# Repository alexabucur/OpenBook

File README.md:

# OpenBook

## Prezentare generala

Proiectul a fost realizat in cadrul disciplinei _Testarea Sistemelor de Calcul_ si isi propune crearea unui model 3D detaliat pentru o tableta E-Book Reader. Am proiectat atat la nivel de circuit, cat si la nivel de design al produsului, folosind programul _Fusion360_ de la Autodesk.

## Block Diagram

## Bill of Materials
| Device | Description | Datasheet | Price per Unit | Link |
|----------------------|--------------------------------------|-----------|-----------|------|
| ADAFRUIT_LEDCHIP-LED0603 | LED | [datasheet](https://ro.mouser.com/datasheet/2/423/LSM0603412V-1379745.pdf) | 1,50 RON | [link](https://ro.mouser.com/ProductDetail/VCC/LSM0603412V?qs=sGAEpiMZZMt82OzCyDsLFG1ehM2%252BdxqbAopHlSxILTc%3D) |
| SJ | SMD solder JUMPER | [datasheet](https://www.farnell.com/datasheets/2813407.pdf) | 0,01 RON | [link](https://ro.farnell.com/panasonic/erj3gey0r00v/res-0r0-0-1w-0603-thick-film/dp/2059527) |
| ESP32_WROVER_EAGLE-LTSPICE_RR0402 | RESISTOR, European symbol | [datasheet](https://www.vishay.com/doc?28700) | 0,941 RON | [link](https://ro.mouser.com/ProductDetail/Vishay-Beyschlag/MCS04020D9101BE000?qs=sGAEpiMZZMvdGkrng054twKDKoBh%252BscnK%2FuqkNk9X%252BqO%2Fz5%2F0u93Ow%3D%3D) |
| 112A-TAAR-R03_ATTEND | Micro SD Card Socket, Push-Push Type, Top Mount, SMT, H=1.83mm, 10u | [datasheet](https://www.attend.com.tw/data/download/file/112A-TAAR-R03.pdf) | 1,54 RON | [link](https://www.soselectronic.com/ro-ro/products/attend/112a-taar-r03-116052) |
| EAGLE-LTSPICE_CC0402 | CAPACITOR, European symbol | [datasheet](https://ro.mouser.com/datasheet/2/40/Accu_P-3077555.pdf) | 5,74 RON | [link](https://ro.mouser.com/ProductDetail/KYOCERA-AVX/04025J0R5ZBSTR?qs=k4kUdCzLgS7v2DzbDWDPRw%3D%3D) |
| ESP32_WROVER_SPARKFUN-DISCRETESEMI_MOSFET_PCH-DMG2305UX-7 | P-channel MOSFETs | [datasheet](https://www.diodes.com/assets/Datasheets/DMG2305UX.pdf) | 0,941 RON | [link](https://ro.mouser.com/ProductDetail/Diodes-Incorporated/DMG2305UX-7?qs=L1DZKBg7t5F%2FNBHrjfxC%252Bg%3D%3D) |
| 744043680IND_4828-WE-TPC_WRE | | [datasheet](https://www.we-online.com/components/products/datasheet/744043680.pdf) | 6,44 RON | [link](https://ro.mouser.com/ProductDetail/Wurth-Elektronik/744043680?qs=PGXP4M47uW6VkZq%252BkzjrHA%3D%3D)|
| BD5229G-TR | Voltage Detector with Adjustable Delay Time | [datasheet](https://datasheet.datasheetarchive.com/originals/distributors/Datasheets_SAMA/f2b9741ef86007909f138d561a359946.pdf) | 3,72 RON | [link](https://ro.mouser.com/ProductDetail/ROHM-Semiconductor/BD5229G-TR?qs=4kLU8WoGk0vvnhrrYwdszw%3D%3D) |
| CPH3225A | Cap 0.011F 3.3V 1210 Flat | [datasheet](https://ro.mouser.com/datasheet/2/360/Seiko_Instruments_MicroBattery_E_20230330_2024Jan_-3561061.pdf) | 11,04 RON | [link](https://ro.mouser.com/ProductDetail/Seiko-Semiconductors/CPH3225A?qs=3etwrb1wR%252BhUOph6lAO7eg%3D%3D) | 
| DS3231SN# | Real Time Clock Serial 16-Pin SOIC W T/R | [datasheet](https://ro.mouser.com/datasheet/2/609/DS3231-3421123.pdf) | 73,80 RON | [link](https://ro.mouser.com/ProductDetail/Analog-Devices-Maxim-Integrated/DS3231SN?qs=1eQvB6Dk1vhUlr8%2FOrV0Fw%3D%3D) |
| ESP32-C6-WROOM-1-N8 | | [datasheet](https://ro.mouser.com/datasheet/2/891/Espressif_ESP32_C6_WROOM_1__Datasheet_V0_1_PRELIMI-3239987.pdf) | 14,70 RON | [link](https://ro.mouser.com/ProductDetail/Espressif-Systems/ESP32-C6-WROOM-1-N8?qs=8Wlm6%252BaMh8ST02Gmwp74cw%3D%3D) |
| ESP32_WROVER_AVX---SD0805S020S1R0_AVX_ SD0805S020S1R0_0_0AVX_SD0805S020S1R0_0_0 | Schottky Barrier Rectifier Diode | [datasheet](http://datasheets.avx.com/schottky.pdf) | 1,46 RON | [link](https://ro.mouser.com/ProductDetail/KYOCERA-AVX/SD0805S020S1R0?qs=jCA%252BPfw4LHbpkAoSnwrdjw%3D%3D) |
| ESP32_WROVER_BME680_BME680 | Integrated Environmental Unit | [datasheet](https://ro.mouser.com/datasheet/2/783/BST_BME680_DS001-1509608.pdf) | 40,69 RON | [link](https://ro.mouser.com/ProductDetail/Bosch-Sensortec/BME680?qs=v271MhAjFHjo0yA%2FC4OnDQ%3D%3D) |
| ESP32_WROVER_SPARKFUN-IC-POWER_MCP73831 | MCP73831T Li-Ion, Li-Pol Controller | [datasheet](https://ro.mouser.com/datasheet/2/268/MCP73831_Family_Data_Sheet_DS20001984H-3441711.pdf) | 3,57 RON | [link](https://ro.mouser.com/ProductDetail/Microchip-Technology/MCP73831T-4ADI-OT?qs=hH%252BOa0VZEiBTiqxSV9eepQ%3D%3D) |
| FH34SRJ-24S-0.5SH_99_ |  (0.50mm) Surface Mount, Right Angle | [datasheet](https://ro.mouser.com/datasheet/2/185/FH34SRJ_24S_0_5SH_99__CL0580_1255_6_99_2DDrawing_0-1615044.pdf) | 12,87 RON | [link](https://ro.mouser.com/ProductDetail/Hirose-Connector/FH34SRJ-24S-0.5SH99?qs=vcbW%252B4%252BSTIpKBl5ap9J8Fw%3D%3D) |
| MAX17048G+T10 |  | [datasheet](https://ro.mouser.com/datasheet/2/609/MAX17048_MAX17049-3469099.pdf) | 21,19 RON | [link](https://ro.mouser.com/ProductDetail/Analog-Devices-Maxim-Integrated/MAX17048G%2bT10?qs=D7PJwyCwLAoGnnn8jEPRBQ%3D%3D) |
| MBR0530 | ON SEMICONDUCTOR - MBR0530 - DIODE, SCHOTTKY, 0.5A, 30V, SOD-123 | [datasheet](https://www.onsemi.com/PowerSolutions/product.do?id=MBR0530T3G) | 0,89 RON | [link](https://ro.mouser.com/ProductDetail/onsemi/MBR0530T3G?qs=3JMERSakebpEmdUS6GetdQ%3D%3D) |
| PGB1010603MR |  | [datasheet](https://www.littelfuse.com/assetdocs/pulseguard-esd-suppressors-pgb1-datasheet?assetguid=8a337998-d54d-466b-be4e-dc5bcd1f9321) | 1,98 RON | [link](https://ro.mouser.com/ProductDetail/Littelfuse/PGB1010603MR?qs=gu7KAQ731URLg4GSnNNN7Q%3D%3D) |
| QWIIC_CONNECTORJS-1MM | SparkFun I2C Standard Qwiic Connector | [datasheet](https://ro.mouser.com/datasheet/2/813/Qwiic_Connector_Datasheet-1223982.pdf) | 2,75 RON | [link](https://ro.mouser.com/ProductDetail/SparkFun/PRT-14417?qs=wd5RIQLrsJhgdz%2FpmZ%2F3GQ%3D%3D) |
| SAMACSYS_PARTS_USB4110-GF-A | CONN USB 2.0 TYPE-C R/A SMT | [datasheet](https://ro.mouser.com/datasheet/2/837/GCT_USB4110_Product_Drawing___20k_cycles-3455479.pdf) | 5,84 RON | [link](https://ro.mouser.com/ProductDetail/GCT/USB4110-GF-A?qs=KUoIvG%2F9IlYiZvIXQjyJeA%3D%3D) |
| SI1308EDL-T1-GE3 | MOSFET N-Ch 30V 1.5A TrenchFET SC70 Vishay Si1308EDL-T1-GE3 N-channel MOSFET Transistor, 1.5 A, 30 V, 3-Pin SC-70 | [datasheet](https://www.vishay.com/doc?63399) | 2,07 RON | [link](https://ro.mouser.com/ProductDetail/Vishay-Semiconductors/SI1308EDL-T1-GE3?qs=bX1%252BNvsK%2FBramh9tgpOaEw%3D%3D) |
| USBLC6-2SC6Y | Low Cap. ESD Protection Auto SOT-23-6 STMicroelectronics  | [datasheet](https://ro.mouser.com/datasheet/2/389/usblc6_2sc6y-1852505.pdf) | 2,16 RON | [link](https://ro.mouser.com/ProductDetail/STMicroelectronics/USBLC6-2SC6Y?qs=gNDSiZmRJS%2FOgDexvXkdow%3D%3D) |
| W25Q512JVEIQ |  | [datasheet](https://ro.mouser.com/datasheet/2/949/Winbond_W25Q512JV_Datasheet-3240039.pdf) | 28,91 RON | [link](https://ro.mouser.com/ProductDetail/Winbond/W25Q512JVEIQ?qs=l7cgNqFNU1jw6svr3at6tA%3D%3D) |
| XC6220A331MR-G | LDO Voltage Regulators | [datasheet](https://ro.mouser.com/datasheet/2/760/xc6220-3371556.pdf) | 7,23 RON | [link](https://ro.mouser.com/ProductDetail/Torex-Semiconductor/XC6220A331MR-G?qs=AsjdqWjXhJ8ZSWznL1J0gg%3D%3D) |

## Functionalitate hardware
Componentele principale ale circuitului sunt:

+ USB C Connector + ESD Protection
  
 > destinat alimentarii E-Book, se conecteaza prin interfata USB
 
+ SD Card
 
 > Secure Digital Card este folosit ca si mediu de stocare pentru cartile in format electronic; lucreaza la 3.3V si se conecteaza cu microcontrollerul prin interfata SPI
 
+ E-Paper Display, impreuna cu modulele aferente - E-Paper Drive Circuit, E-Paper Display Header, EPD Power
  
> EPD Header se conecteaza prin interfata SPI la microcontroller, si realizeaza legatura intre celelalte componente
> EPD Power furnizeaza tensiuni multiple, iar E-Paper Drive Circuit genereaza semnalele necesare pentru controlul display-ului E-Paper
>
> display-ul consuma cel mai mult la refresh, 30mA daca este alb-negru si pana la 60mA pentru display color, iar in modul inactiv, dupa ce a afisat imaginea, consumul este chiar zero
 
+ Environmental Sensor BME688
  
 > este un senzor de mediu ce poate masura temperatura, umiditatea, presiunea atmosferica si calitatea aerului, care functioneaza la 3.3V si se conecteaza prin interfata I2C
>
> are un consum redus, in standby sub 1uA, iar pentru masurare foloseste intre 1-2mA

+ RTC Module DS3231SN
  
 > este un modul Real-Time Clock care are rolul de a pastra data si ora curenta atunci cand microcontroller-ul este oprit; poate functiona pe baterie, si are un cristal de 32KHz integrat; se conecteaza la ESP32-C6 prin I2C, folosind pinii SCL si SDA
>
> consumul sau tipic variaza de la 150uA, atunci cand este alimentat de la sursa principala, si scade la 1uA la trecerea pe baterie

+ External NOR Flash 64MB
  
> extinde memoria microcontroller-ului, aici se stocheaza date suplimentare, se poate face si o stocare temporara; foloseste interfata SPI
> 
> contributia sa la consumul energetic total este foarte mica; cel mai mult se consuma la stergerea din flash (in jur de 50mA), respectiv la scriere (30-50mA); in standby se consuma numai 10-20uA

+	LDO Voltage Regulator
  
> este un stabilizator de tensiune liniar, care asigura tensiunea de iesire constanta la valoarea de 3.3V pentru microcontroller;
>
> are un consum energetic foarte mic (in jur de 8uA atunci cand este activ), ceea ce il face ideal pentru dispozitive alimentate pe baza de baterie, precum cel de fata

+ Voltage Supervisor
  
> folosit pentru monitorizeaza nivelului tensiunii, si pentru a asigura ca sistemul nu poate porni atunci cand avem o tensiune instabila sau mult prea mica

+ Qwiic/Stemma QT
  
> simplifica atasarea senzorilor si perifericelor la microcontroller, facand posibila conectarea mai multor dispozitive in lant, fara a fi nevoie de fire distincte pentru fiecare semnal; functioneaza pe baza protocolului I2C

+ Li-Po Battery Controller

> gestioneaza incarcarea/descarcarea bateriei, regland constant tensiunea si curentul;  la alimentarea bateriei, previne supraincarcarea , iar la descarcare monitorizeaza tensiunea pentru a evita descarcarea profunda; este conectat la sursa de alimentare si la baterie

## Microcontroller - ESP32-C6
Intreg circuitul a fost conceput in jurul microcontrollerului ESP32-C6-WROOM, care este un modul preasamblat, si principalul consumator energetic al circuitului. Consumul mediu se situeaza undeva intre 100uA si 2mA, avand in vedere ca in modul _Activ_ se consuma in jur de 100-120mA, in _Idle_ 10-15mA iar atunci cand se afla in _Deep Sleep_ doar 10-20uA. In mod evident, consumul depinde cel mai mult de durata sesiunilor active.
> Placa ESP-WROOM-32 dispune de o varietate de interfete pentru conectarea altor componente si senzori, inclusiv pini de I/O, SPI, I2C si UART. Aceastea faciliteaza integrarea si extind gama de aplicatii posibile. Placa foloseste WiFi 6 2.4 GHz, are integrat Bluetooth 5 si antena.
>> 
> ESP32-C6 se leaga de cele mai importante module ale circuitului prin intermediul pinilor sai:
> - **Alimentare si reset**
>> **3V3** asigura alimentrea modulului, **GND** legatura la masa, **EN** trebuie sa fie pe pozitia _HIGH_ pentru ca modulul sa functioneze (EN va fi controlat de catre butonul RESET)
> - **USB C Connector**
>> deoarece ESP32-C6 are USB nativ, conexiunea se realizeaza direct prin liniile de date **USB_D+** si **USB_D-**, la pinii **GPIO13** si **GPIO14** ai modulului; nu mai este deci nevoie de un convertor serial extern
> - **SD Card**
>> pentru a comunica cu dispozitive rapide precum SD Card se foloseste interfata SPI(Serial Peripheral Interface), folosind pinii **GPIO27(MISO)** - pentru transfer de la card la ESP, **GPIO7(MOSI)** - pentru transfer invers, **GPIO6(SCK)** -semnalul de ceas care asigura sincronizarea, respectiv **GPIO4(SS_SD)** - chip select
> - **E-Paper Display**
>> pentru conexiunea si controlul ecranului dispozitivului se folosesc pinii **GPIO11(EPD_CS)** - Chip Select pentru display-ul EPD, **GPIO5(EPD_DC)** - pentru controlul display-ului, **GPIO21(EPD_RST)** - pentru resetarea display-ului, respectiv **GPIO26(EPD_BUSY)**
> - **Environmental Sensor BME688**
>> avand in vedere ca se face comunicatia cu senzorul prin intermediul protocolului I2C, pentru stabilirea legaturii se vor folosi pinii **GPIO19(SDA)**, **GPIO20(SCL)** si **GPIO17(I2C_PW)** de pe microcontroller
> - **UART(Serial Communication)**
>> ESP32-C6 are si interfete seriale, utile pentru debugging sau conexiuni cu alte dispozitive; pinii aferenti comunicarii UART sunt **TXD0** -pentru transmisia datelor respectiv **RXD0** - pentru receptie de date
> - **Restul pinilor**
>> - **FLASH_CS** este un pin Chip Select pentru selectarea chipului flash extern (pentru comunicarea SPI cu External NOR Flash)
>> - **IO/BOOT** folosit pentru a intra in boot mode – legatura cu butonul de _boot_
>> - **RTC_PWM** pentru semnale Pulse Width Modulation trimise catre Real Time Clock
>> - **RTC_RST** pentru resetarea ceasului
>> - **INT_RTC** destinat semnalelor de intrerupere de la modulul RTC, de exemplu in cazul iesirii din moduri de functionare (sleep), pentru executarea unor sarcini periodice, cum ar fi un refresh al display-ului etc.

## Amplasarea componentelor / Reguli de design

La design-ul PCB-ului am tinut cont de cateva aspecte importante in ceea ce priveste amplasarea componentelor pe placuta. Astfel:

+ **Microcontroller-ul ESP32** se afla in marginea de sus a PCB-ului, cu antena inspre exterior si cu PCB-ul decupat in aceasta zona, pentru ca antena sa nu fie blocata si pentru a se evita orice interferente
+ **Conectorul USB** se afla in partea de jos a placutei, centrat astfel incat sa se alinieze cu orificiul din carcasa si sa permita conectarea mufei USB-C
+ **E-Paper Display Header** este pozitionat pe lateral, iar in dreptul sau exista un decupaj in PCB - acesta este spatiul in care se va introduce ribbon-ul display-ului nostru
+  **Conectorul Qwiic** e amplasat pe marginea PCB-ului, si s-a lasat suficient spatiu in jurul sau, pentru a permite conectarea facila a unor cabluri suplimentare
+  PCB-ul este decupat intr-o zona suficient de mare in care sa incapa si bateria device-ului
## Errors

La editarea PCB-ului in Fusion 360 am intampinat urmatoarele erori:

Erorile au aparut din cauza dimensiunii gaurilor din mufa USB, asa ca le-am aprobat pe amandoua.

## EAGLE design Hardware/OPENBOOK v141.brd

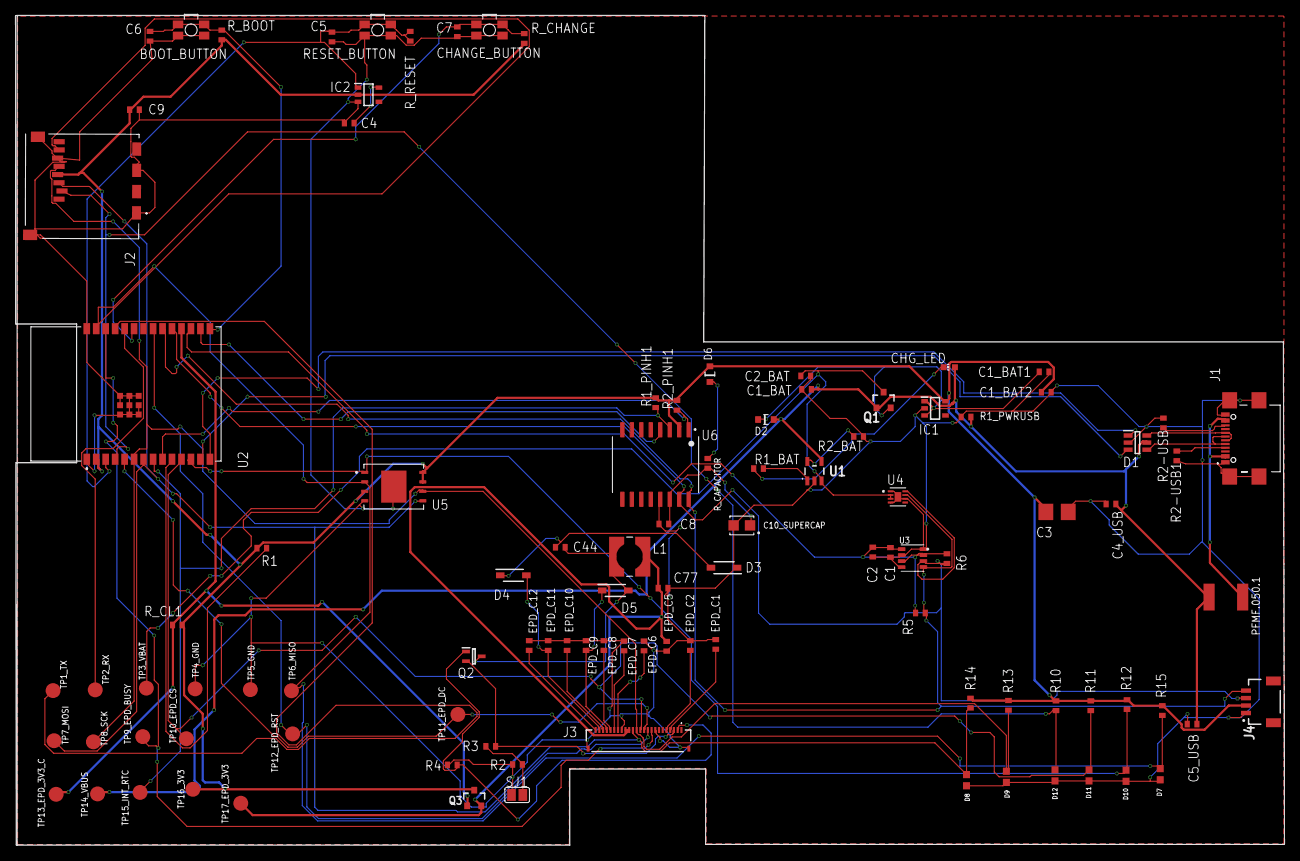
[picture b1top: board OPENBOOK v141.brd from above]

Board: 2 copper layers, 170.1 x 111.2 mm, 103 parts (0 on the bottom side), 55 nets.

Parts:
BOOT_BUTTON: BUTTON_CUSYOMV1; MYBUTTON
C1, C2, C4, C4_USB, C6, C7, C8, C9: 100nF; EAGLE-LTSPICE_C0402
C1_BAT, C1_BAT1, C1_BAT2, C2_BAT, C5_USB: 4.7uF; EAGLE-LTSPICE_C0402
C3: 100uF; RCL_CT3528
C5: 1uF; EAGLE-LTSPICE_C0402
C10_SUPERCAP: CPH3225A; CAPCP3225X100N
C44: 4.7uF/25V; EAGLE-LTSPICE_C0402
C77: 10uF; EAGLE-LTSPICE_C0402
CHANGE_BUTTON: BUTTON_CUSYOMV1; MYBUTTON
CHG_LED: ADAFRUIT_CHIP-LED0603
D1: USBLC6-2SC6Y; SOT95P280X145-6N
D2, D6: ESP32_WROVER_AVX---SD0805S020S1R0_AVX_SD0805S020S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; ESP32_WROVER_AVX---SD0805S020S1R0_AVX_SD0805S020S1R0_0
D3, D4, D5: MBR0530; SOD3716X135N
D7, D8, D9, D10, D11, D12: PGB1010603MR; DIOC1608X36N
EPD_C1, EPD_C2, EPD_C6, EPD_C7, EPD_C8, EPD_C9, EPD_C10, EPD_C11, EPD_C12: 1uF/50V; EAGLE-LTSPICE_C0402
EPD_C5: 0.1uF/50V; EAGLE-LTSPICE_C0402
IC1: XC6220A331MR-G; SOT95P280X120-5N
IC2: BD5229G-TR; SOT95P280X125-5N
J1: SAMACSYS_PARTS_USB4110-GF-A; SAMACSYS_PARTS_USB4110GFA
J2: 112A-TAAR-R03_ATTEND; 112ATAARR03ATTEND
J3: FH34SRJ-24S-0.5SH_99_; FH34SRJ24S05SH99
J4: QWIIC_RIGHT_ANGLE; JST04_1MM_RA
L1: 68uH; IND_4828-WE-TPC_WRE
PFMF.050.1: ESP32C6_VARISTORCN1812; ESP32C6_VARISTOR_CT/CN1812
Q1, Q3: 20V/4.2A/52mΩ/1.4W; ESP32_WROVER_SPARKFUN-DISCRETESEMI_SOT23-3
Q2: SI1308EDL-T1-GE3; SOT65P210X110-3N
R1, R1_PINH1, R2_PINH1, R4, R5, R6, R10, R11, R12, R13, R14, R15: 10K; ESP32_WROVER_EAGLE-LTSPICE_R0402
R1_BAT: 200; ESP32_WROVER_EAGLE-LTSPICE_R0402
R1_PWRUSB: 100K; ESP32_WROVER_EAGLE-LTSPICE_R0402
R2: 2.2; ESP32_WROVER_EAGLE-LTSPICE_R0402
R2-USB, R2-USB1: 5k1; ESP32_WROVER_EAGLE-LTSPICE_R0402
R2_BAT: 2K; ESP32_WROVER_EAGLE-LTSPICE_R0402
R3: 0.47; ESP32_WROVER_EAGLE-LTSPICE_R0402
RESET_BUTTON: BUTTON_CUSYOMV1; MYBUTTON
R_BOOT: 10K; ESP32_WROVER_EAGLE-LTSPICE_R0402
R_CAPACITOR: ESP32_WROVER_EAGLE-LTSPICE_R0402
R_CHANGE: 10K; ESP32_WROVER_EAGLE-LTSPICE_R0402
R_CL1: 10K; ESP32_WROVER_EAGLE-LTSPICE_R0402
R_RESET: 10K; ESP32_WROVER_EAGLE-LTSPICE_R0402
SJ1: SJ
TP1_TX, TP2_RX, TP3_VBAT, TP4_GND, TP5_GND, TP6_MISO, TP7_MOSI, TP8_SCK, TP9_EPD_BUSY, TP10_EPD_CS, TP11_EPD_DC, TP12_EPD_RST, TP13_EPD_3V3_C, TP14_VBUS, TP15_INT_RTC, TP16_3V3, TP17_EPD_3V3: TPTP20R; TP20R
U1: ESP32_WROVER_SPARKFUN-IC-POWER_MCP73831; ESP32_WROVER_SPARKFUN-IC-POWER_SOT23-5
U2: ESP32-C6-WROOM-1-N8; XCVR_ESP32-C6-WROOM-1-N8
U3: ESP32_WROVER_BME680_BME680; ESP32_WROVER_BME680_PSON80P300X300X100-8N
U4: MAX17048G+T10; SON50P200X200X80-9N
U5: W25Q512JVEIQ; SON127P600X800X80-9N
U6: DS3231SN#; SOIC127P1032X265-16N

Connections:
3V3: C1_BAT2.1, C3.+, C9.1, D6.2, IC1.5, IC2.2, J2.P4, J4.2, Q3.3, R1.2, R1_PINH1.2, R2_PINH1.2, R10.2, R11.2, R12.2, R13.2, R14.2, R15.2, R_BOOT.2, R_CHANGE.2, R_CL1.2, TP16_3V3.TP, U2.2, U5.3, U5.7, U5.8, U6.2
32KHZ: R2_PINH1.1, U2.9, U6.1
DN: D1.4, J1.A7, J1.B7
DP: D1.6, J1.A6, J1.B6
EPD_3V3: C77.1, EPD_C5.1, J3.15, J3.16, L1.2, Q3.2, TP17_EPD_3V3.TP
EPD_3V3_C: Q3.1, R_CL1.1, TP13_EPD_3V3_C.TP, U2.18
EPD_BUSY: J3.9, TP9_EPD_BUSY.TP, U2.26
EPD_CS: D11.2, J3.12, R11.1, TP10_EPD_CS.TP, U2.11
EPD_DC: J3.11, TP11_EPD_DC.TP, U2.5
EPD_RST: J3.10, TP12_EPD_RST.TP, U2.21
FLASH_CS: D10.2, R12.1, U2.12, U5.1
GDR: J3.2, Q2.1, R4.2
GND: BOOT_BUTTON.1, BOOT_BUTTON.2, C1.2, C1_BAT.2, C1_BAT1.2, C1_BAT2.2, C2.2, C2_BAT.2, C3.-, C4.2, C4_USB.2, C5.2, C5_USB.2, C6.2, C7.2, C8.2, C9.2, C10_SUPERCAP.2, C77.2, CHANGE_BUTTON.1, CHANGE_BUTTON.2, D1.2, D3.1, D7.1, D8.1, D9.1, D10.1, D11.1, D12.1, EPD_C1.2, EPD_C2.2, EPD_C5.2, EPD_C6.2, EPD_C7.2, EPD_C8.2, EPD_C9.2, EPD_C10.2, EPD_C11.2, EPD_C12.2, IC1.2, IC2.3, J1.A1, J1.A12, J1.B1, J1.B12, J1.MP1, J1.MP2, J1.MP3, J1.MP4, J2.G1, J2.G2, J2.G3, J2.G4, J2.P6, J3.8, J3.17, J3.MP1, J3.MP2, J4.1, R1_PWRUSB.1, R2.1, R2-USB.2, R2-USB1.1, R2_BAT.1, R4.1, RESET_BUTTON.1, RESET_BUTTON.2, SJ1.1, TP4_GND.TP, TP5_GND.TP, U1.2, U2.1, U2.28, U2.29_1, U2.29_2, U2.29_3, U2.29_4, U2.29_5, U2.29_6, U2.29_7, U2.29_8, U2.29_9, U3.1, U3.5, U3.7, U4.1, U4.4, U4.6, U4.9, U5.4, U5.9, U6.13
GPIO8: R1.1, U2.10
I2C_PW: C1.1, C2.1, R5.2, R6.2, U2.17, U3.2, U3.6, U3.8
INT_RTC: R1_PINH1.1, TP15_INT_RTC.TP, U2.8, U6.3
IO/BOOT: BOOT_BUTTON.3, BOOT_BUTTON.4, C6.1, R_BOOT.1, U2.15
IO/CHANGE: C7.1, CHANGE_BUTTON.3, CHANGE_BUTTON.4, R_CHANGE.1, U2.23
MISO: D7.2, J2.P7, R15.1, TP6_MISO.TP, U2.27, U5.2
MOSI: D8.2, J2.P3, J3.14, R14.1, TP7_MOSI.TP, U2.7, U5.5
unnamed: J1.B5, R2-USB.1
unnamed: C1_BAT1.1, D2.1, IC1.1, IC1.3, Q1.2
unnamed: R1_BAT.2, U1.1
unnamed: CHG_LED.C, R1_BAT.1
unnamed: EPD_C1.1, J3.4
unnamed: R2_BAT.2, U1.5
unnamed: EPD_C2.1, J3.5
unnamed: C44.1, D3.2, D4.1
unnamed: J1.A5, R2-USB1.2
unnamed: C4.1, IC2.5
unnamed: EPD_C6.1, J3.18
unnamed: EPD_C7.1, J3.19
unnamed: EPD_C8.1, J3.20
unnamed: EPD_C10.1, J3.22
unnamed: EPD_C12.1, J3.24
unnamed: D6.1, R_CAPACITOR.1
PREVGH: D5.1, EPD_C9.1, J3.21
PREVGL: D4.2, EPD_C11.1, J3.23
RESE: J3.3, Q2.2, R3.2
RESE': R2.2, R3.1, SJ1.2
RESET: C5.1, IC2.1, RESET_BUTTON.3, RESET_BUTTON.4, R_RESET.1, R_RESET.2, U2.3
RTC_RST: U2.16, U6.4
RX: TP2_RX.TP, U2.24
SCK: D9.2, J2.P5, J3.13, R13.1, TP8_SCK.TP, U2.6, U5.6
SCL: J4.4, R5.1, U2.20, U3.4, U4.7, U6.16
SDA: J4.3, R6.1, U2.19, U3.3, U4.8, U6.15
SRC: C44.2, D5.2, L1.1, Q2.3
SS_SD: D12.2, J2.P2, R10.1, U2.4
TX: TP1_TX.TP, U2.25
USB_D+: D1.1, U2.14
USB_D-: D1.3, U2.13
VBAT: C2_BAT.1, Q1.3, TP3_VBAT.TP, U1.3, U4.2, U4.3
VBUS: C1_BAT.1, C4_USB.1, C5_USB.1, CHG_LED.A, D1.5, D2.2, PFMF.050.1.2, Q1.1, R1_PWRUSB.2, TP14_VBUS.TP, U1.4
VRTC: C8.1, C10_SUPERCAP.1, R_CAPACITOR.2, U6.14
VUSB: J1.A4, J1.A9, J1.B4, J1.B9, PFMF.050.1.1

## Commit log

2025-04-02 Revert "Add files via upload"
    This reverts commit a9a9308b9e2a7bee482ae121eab3f34071be44bb.
2025-04-03 Add mechanical folder
2025-04-14 Solved issues

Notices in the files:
parts and their libraries:
COPYRIGHT: Copyright (C) 2024 Ultra Librarian. All rights reserved.
